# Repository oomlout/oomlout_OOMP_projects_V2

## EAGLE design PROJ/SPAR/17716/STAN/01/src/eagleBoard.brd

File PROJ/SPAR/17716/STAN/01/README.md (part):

Contents
========

* [PRPR17716 > Qwiic Time of Flight TMF8801](#prpr17716--qwiic-time-of-flight-tmf8801)
	* [OOMP Parts](#oomp-parts)
	* [Images](#images)
	* [Tags](#tags)
  
![][im]
# PRPR17716 > Qwiic Time of Flight TMF8801

- ID: PROJ-SPAR-17716-STAN-01
- Hex ID: PRPR17716
- Name: Qwiic Time of Flight TMF8801
- Path: oomlout_OOMP_projects_V2/PROJ/SPAR/17716/STAN/01/
- Description: Qwiic Time of Flight TMF8801
- Long Link: [http://oom.lt/PROJ-SPAR-17716-STAN-01](http://oom.lt/PROJ-SPAR-17716-STAN-01)
- Short Link: [http://oom.lt/PRPR17716](http://oom.lt/PRPR17716)

## OOMP Parts

|Image|OOMP ID|Designators|
| :--- | :--- | :--- |
||[CAPC-0603-X-NF100-V50](https://github.com/oomlout/oomlout_OOMP_parts_V2/tree/main/CAPC/0603/X/NF100/V50/)|[C3,C2,C1](https://github.com/oomlout/oomlout_OOMP_parts_V2/tree/main/CAPC/0603/X/NF100/V50/)|
||[HEAD-I01-X-PI04-01](https://github.com/oomlout/oomlout_OOMP_parts_V2/tree/main/HEAD/I01/X/PI04/01/)|[J4,J3](https://github.com/oomlout/oomlout_OOMP_parts_V2/tree/main/HEAD/I01/X/PI04/01/)|
||[HEAD-JSTSH-X-PI04-RS](https://github.com/oomlout/oomlout_OOMP_parts_V2/tree/main/HEAD/JSTSH/X/PI04/RS/)|[J1,J2](https://github.com/oomlout/oomlout_OOMP_parts_V2/tree/main/HEAD/JSTSH/X/PI04/RS/)|
||[LEDS-0603-R-STAN-01](https://github.com/oomlout/oomlout_OOMP_parts_V2/tree/main/LEDS/0603/R/STAN/01/)|[D1](https://github.com/oomlout/oomlout_OOMP_parts_V2/tree/main/LEDS/0603/R/STAN/01/)|
||[RESE-0603-X-O102-01](https://github.com/oomlout/oomlout_OOMP_parts_V2/tree/main/RESE/0603/X/O102/01/)|[R5](https://github.com/oomlout/oomlout_OOMP_parts_V2/tree/main/RESE/0603/X/O102/01/)|
||[RESE-0603-X-O103-01](https://github.com/oomlout/oomlout_OOMP_parts_V2/tree/main/RESE/0603/X/O103/01/)|[R3,R4](https://github.com/oomlout/oomlout_OOMP_parts_V2/tree/main/RESE/0603/X/O103/01/)|
||[RESE-0603-X-O222-01](https://github.com/oomlout/oomlout_OOMP_parts_V2/tree/main/RESE/0603/X/O222/01/)|[R1,R2](https://github.com/oomlout/oomlout_OOMP_parts_V2/tree/main/RESE/0603/X/O222/01/)|
||UNMATCHED-UNMATCHED-X-UNMATCHED-01|U1|
||||

## Images

|kicadPcb3dFront<br>|kicadPcb3dBack<br>|kicadPcb3d<br>|pcbdraw<br>|
| :---: | :---: | :---: | :---: |
|pcbdrawBack<br>||||

## Tags

|Tag Name|Tag Code|Tag Value|
| :--- | :--- | :--- |
|OOMP Type|oompType|PROJ|
|OOMP Size|oompSize|SPAR|
|OOMP Color|oompColor|17716|
|OOMP Description|oompDesc|STAN|
|OOMP Index|oompIndex|01|
|Full OOMP ID|oompID|PROJ-SPAR-17716-STAN-01|
|Hex ID (short code)|hexID|PRPR17716|
|name|name|Qwiic Time of Flight TMF8801|
|gitRepo|gitRepo|https://github.com/sparkfun/Qwiic_Time-of-Flight-TMF8801|
|gitName|gitName|Qwiic_Time-of-Flight-TMF8801|
|eagleBoard|eagleBoard|/Hardware/Qwiic_TMF8801.brd|
|eagleSchem|eagleSchem|/Hardware/Qwiic_TMF8801.sch|
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
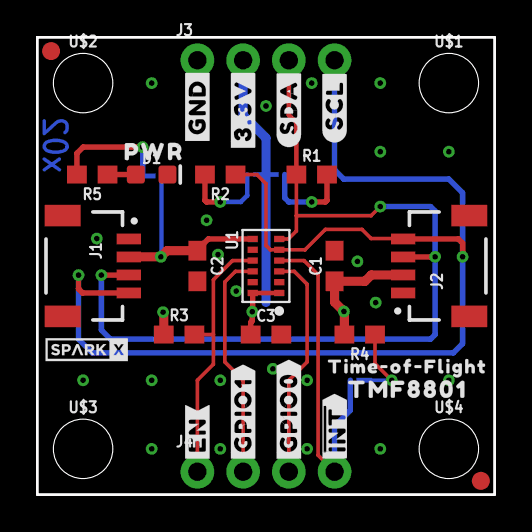
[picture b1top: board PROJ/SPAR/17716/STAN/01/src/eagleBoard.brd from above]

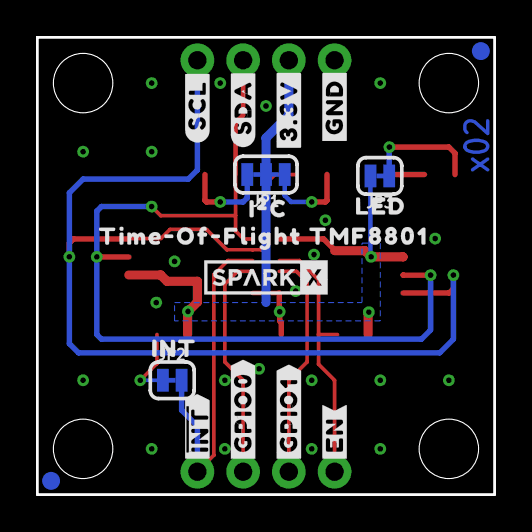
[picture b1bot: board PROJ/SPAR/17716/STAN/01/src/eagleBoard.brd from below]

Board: 2 copper layers, 25.4 x 25.4 mm, 51 parts (18 on the bottom side), 13 nets.

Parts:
C1, C2, C3: 0.1uF; 0603
D1: RED; LED-0603
FD1, FD2, FD3, FD4: FIDUCIAL1X2; FIDUCIAL-1X2
FRAME1: FRAME-LETTERNO_PACKAGE; DUMMY
J1, J2: Qwiic; JST04_1MM_RA
J3, J4: 1X04_NO_SILK
JP1: JUMPER-SMT_3_2-NC_TRACE_SILK; SMT-JUMPER_3_2-NC_TRACE_SILK
JP2, JP3: JUMPER-SMT_2_NC_TRACE_SILK; SMT-JUMPER_2_NC_TRACE_SILK
R1, R2: 2.2k; 0603
R3, R4: 10k; 0603
R5: 1k; 0603
U1: TMF8801; TMF8801-CUSTOM
U$1, U$2, U$3, U$4: STAND-OFF
U$5, U$17: #3#3V#1
U$6, U$19: #SDA#4
U$7, U$18: #GND#0
U$8, U$24: ##INT##7
U$9, U$25: #GPIO0#7
U$10, U$26: #GPIO1#7
U$11, U$23: #EN#6
U$12: #INT0
U$13: TMF88010
U$14: TIME#OF#FLIGHT0
U$16: TIME#OF#FLIGHT_TMF88018
U$20: SPARKX-TINY
U$21, U$22: #SCL#5
U$27: SPARKX-SMALL
U$28: I�C0
U$29: LED1
U$30: PWR2

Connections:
3.3V: C1.1, C2.1, C3.1, J1.2, J2.2, J3.2, JP1.2, JP3.2, R3.2, R4.2, U1.1, U1.7, U1.12
!INT: J4.4, JP2.2, U1.4
EN: J4.1, R3.1, U1.9
GND: C1.2, C2.2, C3.2, D1.C, J1.1, J2.1, J3.1, U1.2, U1.8, U1.11
GPIO0: J4.3, U1.3
GPIO1: J4.2, U1.10
unnamed: D1.A, R5.1
unnamed: JP1.3, R1.2
unnamed: JP1.1, R2.2
unnamed: JP3.1, R5.2
unnamed: JP2.1, R4.1
SCL: J1.4, J2.4, J3.4, R2.1, U1.5
SDA: J1.3, J2.3, J3.3, R1.1, U1.6

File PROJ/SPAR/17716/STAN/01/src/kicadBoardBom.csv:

"Id";"Designator";"Package";"Quantity";"Designation";"Supplier and ref";
1;"FRAME1";"DUMMY";1;"FRAME-LETTERNO_PACKAGE";;;
2;"U$3,U$4,U$2,U$1";"STAND-OFF";4;"";;;
3;"U$5,U$17";"#3#3V#1";2;"";;;
4;"FD1,FD3,FD2,FD4";"FIDUCIAL-1X2";4;"FIDUCIAL1X2";;;
5;"U$14";"TIME#OF#FLIGHT0";1;"";;;
6;"U1";"TMF8801-CUSTOM";1;"TMF8801";;;
7;"D1";"LED-0603";1;"RED";;;
8;"U$8,U$24";"##INT##7";2;"";;;
9;"J4,J3";"1X04_NO_SILK";2;"";;;
10;"U$13";"TMF88010";1;"";;;
11;"U$20";"SPARKX-TINY";1;"";;;
12;"R3,R4";"0603";2;"10k";;;
13;"C3,C2,C1";"0603";3;"0.1uF";;;
14;"U$9,U$25";"#GPIO0#7";2;"";;;
15;"R1,R2";"0603";2;"2.2k";;;
16;"J1,J2";"JST04_1MM_RA";2;"Qwiic";;;
17;"R5";"0603";1;"1k";;;
18;"U$7,U$18";"#GND#0";2;"";;;
19;"U$11,U$23";"#EN#6";2;"";;;
20;"U$6,U$19";"#SDA#4";2;"";;;
21;"U$21,U$22";"#SCL#5";2;"";;;
22;"U$10,U$26";"#GPIO1#7";2;"";;;
23;"U$30";"PWR2";1;"";;;
24;"JP3,JP2";"SMT-JUMPER_2_NC_TRACE_SILK";2;"JUMPER-SMT_2_NC_TRACE_SILK";;;
25;"U$29";"LED1";1;"";;;
26;"U$27";"SPARKX-SMALL";1;"";;;
27;"U$16";"TIME#OF#FLIGHT_TMF88018";1;"";;;
28;"JP1";"SMT-JUMPER_3_2-NC_TRACE_SILK";1;"JUMPER-SMT_3_2-NC_TRACE_SILK";;;
29;"U$28";"I�C0";1;"";;;
30;"U$12";"#INT0";1;"";;;

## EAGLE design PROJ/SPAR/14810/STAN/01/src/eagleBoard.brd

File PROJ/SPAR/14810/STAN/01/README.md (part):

Contents
========

* [PRPR14810 > MP3 Breakout WT2003S](#prpr14810--mp3-breakout-wt2003s)
	* [OOMP Parts](#oomp-parts)
	* [Images](#images)
	* [Tags](#tags)
  
![][im]
# PRPR14810 > MP3 Breakout WT2003S

- ID: PROJ-SPAR-14810-STAN-01
- Hex ID: PRPR14810
- Name: MP3 Breakout WT2003S
- Path: oomlout_OOMP_projects_V2/PROJ/SPAR/14810/STAN/01/
- Description: MP3 Breakout WT2003S
- Long Link: [http://oom.lt/PROJ-SPAR-14810-STAN-01](http://oom.lt/PROJ-SPAR-14810-STAN-01)
- Short Link: [http://oom.lt/PRPR14810](http://oom.lt/PRPR14810)

## OOMP Parts

|Image|OOMP ID|Designators|
| :--- | :--- | :--- |
||[CAPC-0603-X-NF100-V50](https://github.com/oomlout/oomlout_OOMP_parts_V2/tree/main/CAPC/0603/X/NF100/V50/)|[C8,C7](https://github.com/oomlout/oomlout_OOMP_parts_V2/tree/main/CAPC/0603/X/NF100/V50/)|
||CAPC-0603-X-NF220-V25|C6,C3|
||[CAPC-0603-X-UF1-V50](https://github.com/oomlout/oomlout_OOMP_parts_V2/tree/main/CAPC/0603/X/UF1/V50/)|[C5,C4,C9](https://github.com/oomlout/oomlout_OOMP_parts_V2/tree/main/CAPC/0603/X/UF1/V50/)|
||[CAPC-0603-X-UF10-V10](https://github.com/oomlout/oomlout_OOMP_parts_V2/tree/main/CAPC/0603/X/UF10/V10/)|[C1](https://github.com/oomlout/oomlout_OOMP_parts_V2/tree/main/CAPC/0603/X/UF10/V10/)|
||[HEAD-I01-X-PI01-01](https://github.com/oomlout/oomlout_OOMP_parts_V2/tree/main/HEAD/I01/X/PI01/01/)|[J3](https://github.com/oomlout/oomlout_OOMP_parts_V2/tree/main/HEAD/I01/X/PI01/01/)|
||[HEAD-I01-X-PI02-01](https://github.com/oomlout/oomlout_OOMP_parts_V2/tree/main/HEAD/I01/X/PI02/01/)|[J4,JP12](https://github.com/oomlout/oomlout_OOMP_parts_V2/tree/main/HEAD/I01/X/PI02/01/)|
||[HEAD-I01-X-PI03-01](https://github.com/oomlout/oomlout_OOMP_parts_V2/tree/main/HEAD/I01/X/PI03/01/)|[JP10](https://github.com/oomlout/oomlout_OOMP_parts_V2/tree/main/HEAD/I01/X/PI03/01/)|
||[HEAD-I01-X-PI04-01](https://github.com/oomlout/oomlout_OOMP_parts_V2/tree/main/HEAD/I01/X/PI04/01/)|[J2](https://github.com/oomlout/oomlout_OOMP_parts_V2/tree/main/HEAD/I01/X/PI04/01/)|
||HEAD-I01-X-UNMATCHED-01|J1|
||HEAD-UNMATCHED-X-UNMATCHED-01|J8|
||[LEDS-0603-R-STAN-01](https://github.com/oomlout/oomlout_OOMP_parts_V2/tree/main/LEDS/0603/R/STAN/01/)|[D1](https://github.com/oomlout/oomlout_OOMP_parts_V2/tree/main/LEDS/0603/R/STAN/01/)|
||[RESE-0603-X-O102-01](https://github.com/oomlout/oomlout_OOMP_parts_V2/tree/main/RESE/0603/X/O102/01/)|[R2](https://github.com/oomlout/oomlout_OOMP_parts_V2/tree/main/RESE/0603/X/O102/01/)|
||[RESE-0603-X-O103-01](https://github.com/oomlout/oomlout_OOMP_parts_V2/tree/main/RESE/0603/X/O103/01/)|[R5,R10,R9,R1](https://github.com/oomlout/oomlout_OOMP_parts_V2/tree/main/RESE/0603/X/O103/01/)|
||[RESE-0603-X-O222-01](https://github.com/oomlout/oomlout_OOMP_parts_V2/tree/main/RESE/0603/X/O222/01/)|[R4](https://github.com/oomlout/oomlout_OOMP_parts_V2/tree/main/RESE/0603/X/O222/01/)|
||RESE-0603-X-O472-01|R11|
||UNMATCHED-UNMATCHED-X-UNMATCHED-01|U2,U1|
||USBS-UNMATCHED-X-UNMATCHED-01|J6|
||||

## Images

|kicadPcb3dFront<br>|kicadPcb3dBack<br>|kicadPcb3d<br>|pcbdraw<br>|
| :---: | :---: | :---: | :---: |
|pcbdrawBack<br>||||

## Tags

|Tag Name|Tag Code|Tag Value|
| :--- | :--- | :--- |
|OOMP Type|oompType|PROJ|
|OOMP Size|oompSize|SPAR|
|OOMP Color|oompColor|14810|
|OOMP Description|oompDesc|STAN|
|OOMP Index|oompIndex|01|
|Full OOMP ID|oompID|PROJ-SPAR-14810-STAN-01|
|Hex ID (short code)|hexID|PRPR14810|
|name|name|MP3 Breakout WT2003S|
|gitRepo|gitRepo|https://github.com/sparkfun/MP3_Breakout_WT2003S|
|gitName|gitName|MP3_Breakout_WT2003S|
|eagleBoard|eagleBoard|/Hardware/MP3 Breakout.brd|
|eagleSchem|eagleSchem|/Hardware/MP3 Breakout.sch|
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
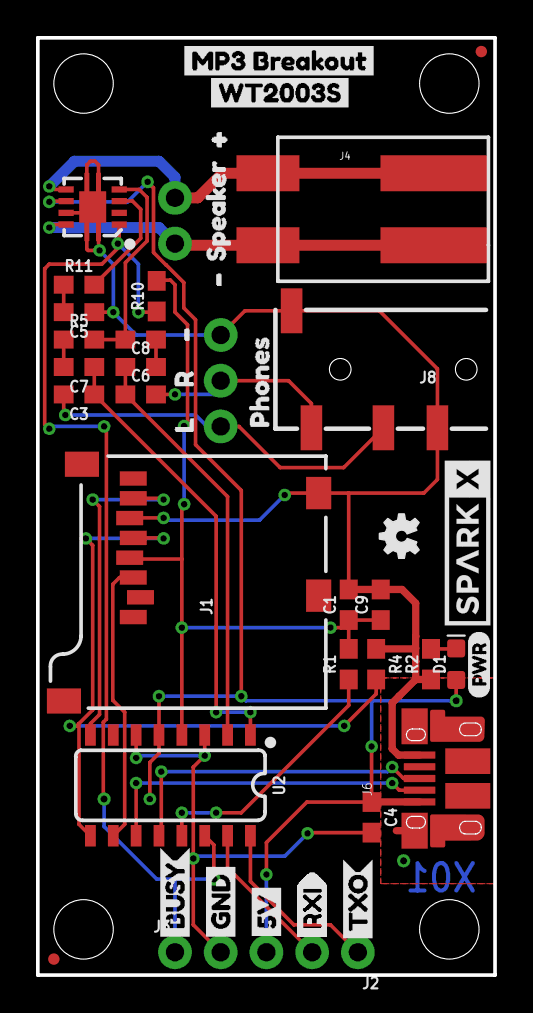
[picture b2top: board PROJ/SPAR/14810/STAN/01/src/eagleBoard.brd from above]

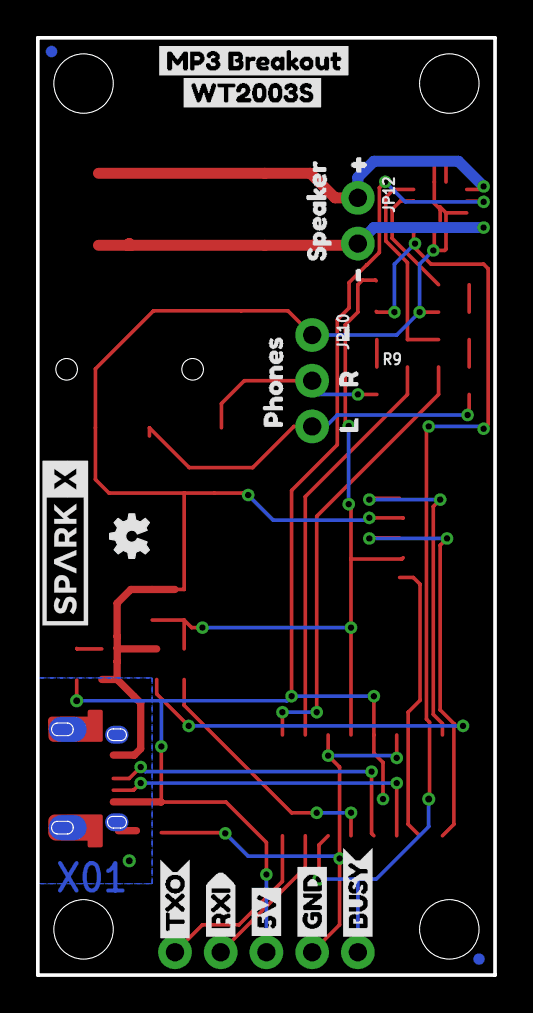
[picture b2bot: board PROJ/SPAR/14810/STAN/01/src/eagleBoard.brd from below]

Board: 2 copper layers, 25.4 x 52.1 mm, 69 parts (20 on the bottom side), 25 nets.

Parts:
C1: 10uF; 0603
C3, C6: 0.22uF; 0603
C4, C5, C9: 1.0uF; 0603
C7, C8: 0.1uF; 0603
D1: RED; LED-0603
FRAME1: FRAME-LETTER; CREATIVE_COMMONS
J1: MICRO-SD; MICRO-SD-SOCKET
J2: Header; 1X04_NO_SILK
J3: 1X01_NO_SILK
J4: Poke-Home; 1X02_POKEHOME
J6: USB-MICROB-PTH-MILL
J8: 3.5mm Audio; AUDIO_JACK_3.5MM_TRRS_SMD_RA
JP1, JP2, JP5, JP6: FIDUCIALUFIDUCIAL; MICRO-FIDUCIAL
JP3, JP4, JP11, JP13: STAND-OFF
JP10: PTH; 1X03_NO_SILK
JP12: PTH; 1X02_NO_SILK
LOGO1: OSHW-LOGOMINI; OSHW-LOGO-MINI
LOGO2: OSHW-LOGOMINI; OSHW-LOGO-MINI@1
R1, R5, R9, R10: 10k; 0603
R2: 1k; 0603
R4: 2.2k; 0603
R11: 100k; 0603
U1: TPA2005D1; QFN-8_PAD
U2: WT2003S; SO16
U$1, U$22: GND1
U$2, U$11: SPARKX-LOGO4; SPARKX-MEDIUM
U$3, U$41: L12
U$4, U$39: R11
U$6, U$9: TXO0
U$7, U$8, U$23: RXI0
U$10, U$15, U$21, U$25: #6
U$12, U$24: MP3_BREAKOUT0
U$13, U$14: BUSY0
U$16, U$40: PHONES0
U$17: PWR-()-03
U$18, U$20: SPEAKER1
U$19, U$28: #5
U$26, U$27: WT2003S0
U$29, U$30: 5V0

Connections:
5V: C4.1, D1.A, J2.3, J6.VBUS, U1.6, U2.5
!SDN: J3.1, R10.1, U1.1, U2.14
AC-L: C3.2, J8.RING1, JP10.3
AC-R: C6.2, J8.TIP, JP10.2
ADKEY: R1.1, U2.13
D+: J6.D+, U2.12
D-: J6.D-, U2.11
GND: C1.2, C4.2, C5.1, C9.2, J1.CD1, J1.GND, J2.4, J6.GND, J8.EARTH, J8.RING2, JP10.1, R2.1, R4.1, U1.7, U1.9, U1.10, U1.11, U1.12, U1.13, U2.3, U2.6
IN+AMP: R11.2, U1.3
IN-AMP: R5.2, R9.2, U1.4
MP3-RXI: J2.2, U2.15
MP3-TXO: J2.1, U2.16
unnamed: D1.C, R2.2
unnamed: C8.2, R9.1
unnamed: C5.2, R11.1
unnamed: C7.2, R5.1
OUT+: J4.P2, J4.P4, JP12.1, U1.5
OUT-: J4.P1, J4.P3, JP12.2, U1.8
SD_CLK: J1.SCLK, R4.2, U2.9
SD_CMD: J1.DI, U2.10
SD_DAT: J1.DO, U2.8
SHLD: J6.SHIELD, J6.SHIELD2, J6.SHIELD3, J6.SHIELD4, J6.SHIELD5, J6.SHIELD6, J6.SHIELD7, J6.SHIELD8, J6.SHIELD9, J6.SHIELD10
VCCIO: C1.1, C9.1, J1.VCC, R1.2, R10.2, U2.4
VOUTL: C3.1, C7.1, U2.1
VOUTR: C6.1, C8.1, U2.2

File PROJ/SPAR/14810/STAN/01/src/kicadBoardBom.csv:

"Id";"Designator";"Package";"Quantity";"Designation";"Supplier and ref";
1;"U$41,U$3";"L12";2;"";;;
2;"C8,C7";"0603";2;"0.1uF";;;
3;"J2";"1X04_NO_SILK";1;"Header";;;
4;"JP4,JP11,JP13,JP3";"STAND-OFF";4;"STAND-OFF";;;
5;"U$20,U$18";"SPEAKER1";2;"";;;
6;"U$10,U$25,U$21,U$15";"#6";4;"";;;
7;"R5,R10,R9,R1";"0603";4;"10k";;;
8;"J4";"1X02_POKEHOME";1;"Poke-Home";;;
9;"J3";"1X01_NO_SILK";1;"";;;
10;"FRAME1";"CREATIVE_COMMONS";1;"FRAME-LETTER";;;
11;"U$12,U$24";"MP3_BREAKOUT0";2;"";;;
12;"J8";"AUDIO_JACK_3.5MM_TRRS_SMD_RA";1;"3.5mm Audio";;;
13;"U$29,U$30";"5V0";2;"";;;
14;"U$23,U$7,U$8";"RXI0";3;"";;;
15;"R4";"0603";1;"2.2k";;;
16;"U$13,U$14";"BUSY0";2;"";;;
17;"D1";"LED-0603";1;"RED";;;
18;"U$26,U$27";"WT2003S0";2;"";;;
19;"C5,C4,C9";"0603";3;"1.0uF";;;
20;"U2";"SO16";1;"WT2003S";;;
21;"R2";"0603";1;"1k";;;
22;"C6,C3";"0603";2;"0.22uF";;;
23;"U1";"QFN-8_PAD";1;"TPA2005D1";;;
24;"U$6,U$9";"TXO0";2;"";;;
25;"U$39,U$4";"R11";2;"";;;
26;"U$2,U$11";"SPARKX-MEDIUM";2;"SPARKX-LOGO4";;;
27;"U$22,U$1";"GND1";2;"";;;
28;"JP1,JP5,JP6,JP2";"MICRO-FIDUCIAL";4;"FIDUCIALUFIDUCIAL";;;
29;"U$17";"PWR-()-03";1;"";;;
30;"J1";"MICRO-SD-SOCKET";1;"MICRO-SD";;;
31;"U$28,U$19";"#5";2;"";;;
32;"J6";"USB-MICROB-PTH-MILL";1;"";;;
33;"R11";"0603";1;"4.7k";;;
34;"C1";"0603";1;"10uF";;;
35;"U$40,U$16";"PHONES0";2;"";;;
36;"LOGO1";"OSHW-LOGO-MINI";1;"OSHW-LOGOMINI";;;
37;"JP10";"1X03_NO_SILK";1;"PTH";;;
38;"LOGO2";"OSHW-LOGO-MINI@1";1;"OSHW-LOGOMINI";;;
39;"JP12";"1X02_NO_SILK";1;"PTH";;;

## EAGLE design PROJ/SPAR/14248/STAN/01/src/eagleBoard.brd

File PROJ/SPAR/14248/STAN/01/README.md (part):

Contents
========

* [PRPR14248 > Qwiic Accelerometer MMA8452Q](#prpr14248--qwiic-accelerometer-mma8452q)
	* [OOMP Parts](#oomp-parts)
	* [Images](#images)
	* [Tags](#tags)
  
![][im]
# PRPR14248 > Qwiic Accelerometer MMA8452Q

- ID: PROJ-SPAR-14248-STAN-01
- Hex ID: PRPR14248
- Name: Qwiic Accelerometer MMA8452Q
- Path: oomlout_OOMP_projects_V2/PROJ/SPAR/14248/STAN/01/
- Description: Qwiic Accelerometer MMA8452Q
- Long Link: [http://oom.lt/PROJ-SPAR-14248-STAN-01](http://oom.lt/PROJ-SPAR-14248-STAN-01)
- Short Link: [http://oom.lt/PRPR14248](http://oom.lt/PRPR14248)

## OOMP Parts

|Image|OOMP ID|Designators|
| :--- | :--- | :--- |
||[CAPC-0603-X-NF100-V50](https://github.com/oomlout/oomlout_OOMP_parts_V2/tree/main/CAPC/0603/X/NF100/V50/)|[C1,C4](https://github.com/oomlout/oomlout_OOMP_parts_V2/tree/main/CAPC/0603/X/NF100/V50/)|
||[CAPC-0603-X-UF47D-V16](https://github.com/oomlout/oomlout_OOMP_parts_V2/tree/main/CAPC/0603/X/UF47D/V16/)|[C5](https://github.com/oomlout/oomlout_OOMP_parts_V2/tree/main/CAPC/0603/X/UF47D/V16/)|
||[HEAD-I01-X-PI02-01](https://github.com/oomlout/oomlout_OOMP_parts_V2/tree/main/HEAD/I01/X/PI02/01/)|[J1](https://github.com/oomlout/oomlout_OOMP_parts_V2/tree/main/HEAD/I01/X/PI02/01/)|
||[HEAD-I01-X-PI04-01](https://github.com/oomlout/oomlout_OOMP_parts_V2/tree/main/HEAD/I01/X/PI04/01/)|[J3](https://github.com/oomlout/oomlout_OOMP_parts_V2/tree/main/HEAD/I01/X/PI04/01/)|
||[HEAD-JSTSH-X-PI04-RS](https://github.com/oomlout/oomlout_OOMP_parts_V2/tree/main/HEAD/JSTSH/X/PI04/RS/)|[J2,J4](https://github.com/oomlout/oomlout_OOMP_parts_V2/tree/main/HEAD/JSTSH/X/PI04/RS/)|
||[RESE-0603-X-O103-01](https://github.com/oomlout/oomlout_OOMP_parts_V2/tree/main/RESE/0603/X/O103/01/)|[R2](https://github.com/oomlout/oomlout_OOMP_parts_V2/tree/main/RESE/0603/X/O103/01/)|
||RESE-0603-X-O472-01|R5,R4|
||UNMATCHED-UNMATCHED-X-UNMATCHED-01|U2|
||||

## Images

|kicadPcb3dFront<br>|kicadPcb3dBack<br>|kicadPcb3d<br>|pcbdraw<br>|
| :---: | :---: | :---: | :---: |
|pcbdrawBack<br>||||

## Tags

|Tag Name|Tag Code|Tag Value|
| :--- | :--- | :--- |
|OOMP Type|oompType|PROJ|
|OOMP Size|oompSize|SPAR|
|OOMP Color|oompColor|14248|
|OOMP Description|oompDesc|STAN|
|OOMP Index|oompIndex|01|
|Full OOMP ID|oompID|PROJ-SPAR-14248-STAN-01|
|Hex ID (short code)|hexID|PRPR14248|
|name|name|Qwiic Accelerometer MMA8452Q|
|gitRepo|gitRepo|https://github.com/sparkfun/Qwiic_Accelerometer-MMA8452Q|
|gitName|gitName|Qwiic_Accelerometer-MMA8452Q|
|eagleBoard|eagleBoard|/Hardware/Qwiic_Accelerometer-MMA8452Q.brd|
|eagleSchem|eagleSchem|/Hardware/Qwiic_Accelerometer-MMA8452Q.sch|
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
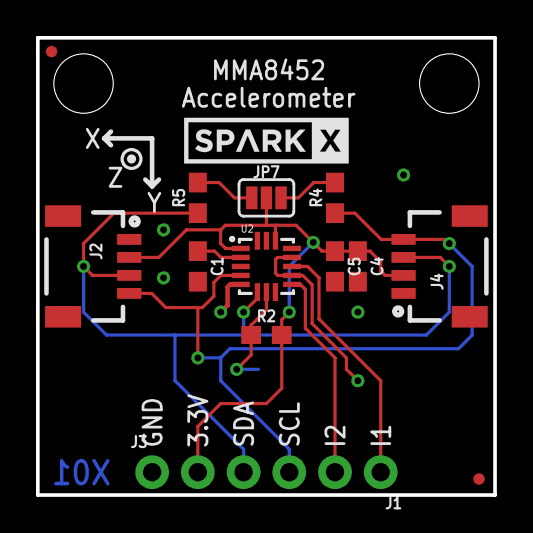
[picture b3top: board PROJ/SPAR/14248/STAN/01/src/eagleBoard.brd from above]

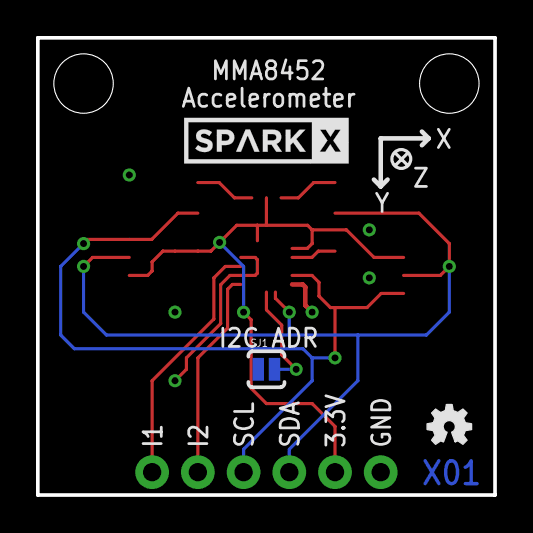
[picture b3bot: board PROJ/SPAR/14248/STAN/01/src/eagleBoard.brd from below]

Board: 2 copper layers, 25.4 x 25.4 mm, 21 parts (3 on the bottom side), 10 nets.

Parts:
C1, C4: 0.1uF; 0603
C5: 4.7uF; 0603
FRAME1: FRAME-LETTER; CREATIVE_COMMONS
J1: 1X02_NO_SILK
J2, J4: SMD; 1X04_1MM_RA
J3: PTH; 1X04_NO_SILK
JP2, JP6: FIDUCIALUFIDUCIAL; MICRO-FIDUCIAL
JP3, JP4: STAND-OFF
JP7: SMT-JUMPER_3_2-NC_PASTE_SILK
LOGO1: OSHW-LOGOMINI; OSHW-LOGO-MINI
R2: 10k; 0603
R4, R5: 4.7k; 0603
SJ1: SJ_2S-NO
U2: MMA8452Q; QFN-16_0.5MM
U$1, U$2: SPARKX-LOGO4; SPARKX-MEDIUM

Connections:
3.3V: C4.1, C5.1, J2.2, J3.2, J4.2, JP7.2, R2.2, U2.1, U2.14
BYP: C1.1, U2.2
GND: C1.2, C4.2, C5.2, J2.1, J3.1, J4.1, SJ1.1, U2.5, U2.10, U2.12
INT1: J1.1, U2.11
INT2: J1.2, U2.9
unnamed: JP7.1, R5.2
unnamed: JP7.3, R4.2
SA0: R2.1, SJ1.2, U2.7
SCL: J2.4, J3.4, J4.4, R4.1, U2.4
SDA: J2.3, J3.3, J4.3, R5.1, U2.6

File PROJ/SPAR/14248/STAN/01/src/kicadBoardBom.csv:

"Id";"Designator";"Package";"Quantity";"Designation";"Supplier and ref";
1;"JP3,JP4";"STAND-OFF";2;"STAND-OFF";;;
2;"R5,R4";"0603";2;"4.7k";;;
3;"JP7";"SMT-JUMPER_3_2-NC_PASTE_SILK";1;"";;;
4;"JP2,JP6";"MICRO-FIDUCIAL";2;"FIDUCIALUFIDUCIAL";;;
5;"C1,C4";"0603";2;"0.1uF";;;
6;"U2";"QFN-16_0.5MM";1;"MMA8452Q";;;
7;"J3";"1X04_NO_SILK";1;"PTH";;;
8;"J1";"1X02_NO_SILK";1;"";;;
9;"R2";"0603";1;"10k";;;
10;"U$2,U$1";"SPARKX-MEDIUM";2;"SPARKX-LOGO4";;;
11;"FRAME1";"CREATIVE_COMMONS";1;"FRAME-LETTER";;;
12;"C5";"0603";1;"4.7uF";;;
13;"J2,J4";"1X04_1MM_RA";2;"SMD";;;
14;"LOGO1";"OSHW-LOGO-MINI";1;"OSHW-LOGOMINI";;;
15;"SJ1";"SJ_2S-NO";1;"";;;

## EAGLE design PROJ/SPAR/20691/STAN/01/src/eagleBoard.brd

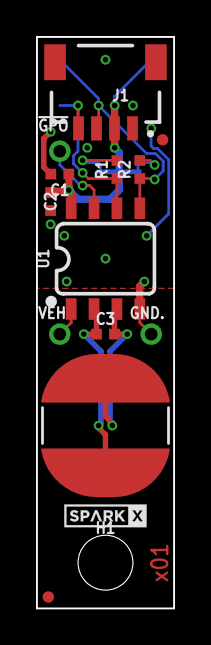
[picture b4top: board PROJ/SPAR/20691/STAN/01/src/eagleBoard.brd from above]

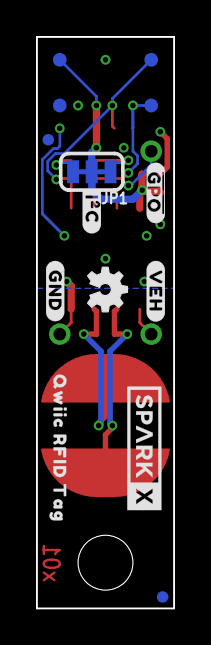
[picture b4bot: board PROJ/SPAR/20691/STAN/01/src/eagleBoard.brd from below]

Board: 2 copper layers, 7.6 x 31.8 mm, 31 parts (14 on the bottom side), 10 nets.

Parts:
3V3: TEST-POINT3; PAD.03X.03
!GPO!: 1X01_1MM_NO_SILK
ANT: 4.7μH; W3102
C1: 0.1uF; 0402-TIGHT
C2: 2.2uF; 0402-TIGHT
C3: 0.5pF; 0402-TIGHT
FD1, FD2, FD3, FD4: FIDUCIALUFIDUCIAL; FIDUCIAL-MICRO
FRAME2: FRAME-LETTER; CREATIVE_COMMONS
GND: TEST-POINT3; PAD.03X.03
GND.: 1X01_1MM_NO_SILK
H1: STAND-OFFTIGHT; STAND-OFF-TIGHT
J1: QWIIC_RIGHT_ANGLE; JST04_1MM_RA
JP1: JUMPER-SMT_3_2-NC_TRACE_SILK; SMT-JUMPER_3_2-NC_TRACE_SILK
LOGO1: SPECIAL_INSTRUCTIONS-ORDERING; ORDERING_INSTRUCTIONS
LOGO2: OSHW-LOGOMINI; OSHW-LOGO-MINI
R1, R2: 2.2k; 0402-TIGHT
SCL: TEST-POINT3; PAD.03X.03
SDA: TEST-POINT3; PAD.03X.03
U1: ST25DV64KC; SO08
U$1: SPARKX-LOGO2; SPARKX-TINY
U$2: ##GPO##0
U$3: QWIIC_RFID_TAG0
U$4: #VEH#0
U$5: #I�C#0
U$6: #GND#0
U$20: SPARKX-LOGO3; SPARKX-SMALL
VEH: 1X01_1MM_NO_SILK

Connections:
3.3V: 3V3.1, C1.1, C2.1, J1.2, JP1.2, U1.8
!GPO!: !GPO!.1, U1.7
GND: C1.2, C2.2, GND.1, GND..1, J1.1, U1.4
unnamed: ANT.2, C3.2, U1.3
unnamed: ANT.1, C3.1, U1.2
unnamed: JP1.3, R2.2
unnamed: JP1.1, R1.2
SCL: J1.4, R1.1, SCL.1, U1.6
SDA: J1.3, R2.1, SDA.1, U1.5
VEH: U1.1, VEH.1

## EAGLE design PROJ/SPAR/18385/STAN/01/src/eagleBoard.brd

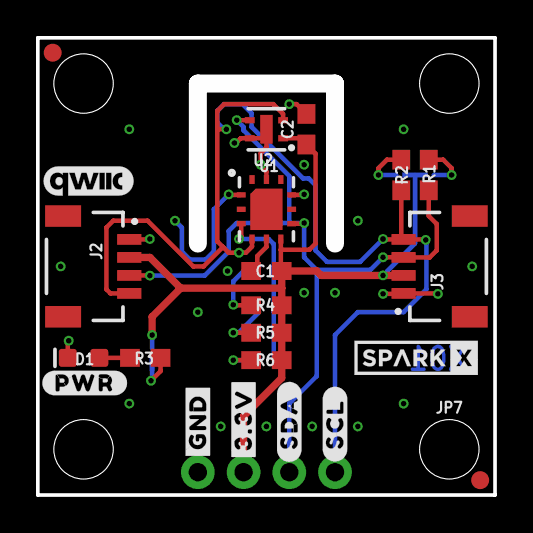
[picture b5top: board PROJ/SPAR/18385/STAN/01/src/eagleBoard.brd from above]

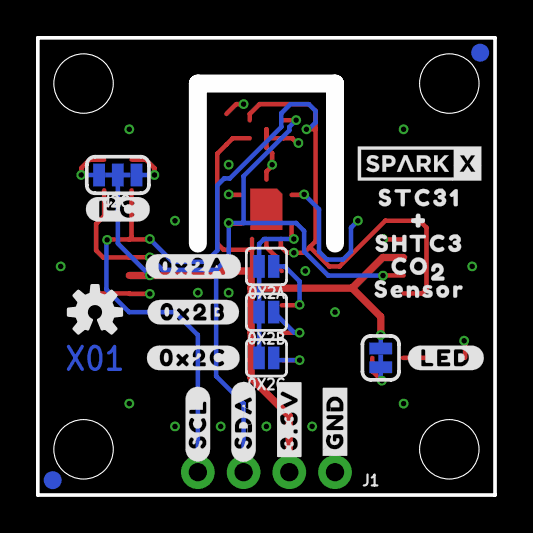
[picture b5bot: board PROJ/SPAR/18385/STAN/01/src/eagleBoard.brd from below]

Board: 2 copper layers, 25.4 x 25.4 mm, 53 parts (25 on the bottom side), 12 nets.

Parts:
0X2A, 0X2B, 0X2C: JUMPER-SMT_2_NO_SILK; SMT-JUMPER_2_NO_SILK
C1, C2: 0.1uF; 0603
D1: RED; LED-0603
FRAME1: FRAME-LETTER; CREATIVE_COMMONS
I2C: JUMPER-SMT_3_2-NC_TRACE_SILK; SMT-JUMPER_3_2-NC_TRACE_SILK
J1: 1X04_NO_SILK
J2, J3: QWIIC_RIGHT_ANGLE; JST04_1MM_RA
JP1, JP2, JP5, JP6: FIDUCIAL1X2; FIDUCIAL-1X2
JP3, JP4, JP7, JP8: STAND-OFF
LED: JUMPER-SMT_2_NC_TRACE_SILK; SMT-JUMPER_2_NC_TRACE_SILK
LOGO1: SPECIAL_INSTRUCTIONS-ORDERING; ORDERING_INSTRUCTIONS
LOGO2: QWIIC_LOGO_5MM; QWIIC_5MM
LOGO5: OSHW-LOGOS; OSHW-LOGO-S
R1, R2: 4.7k; 0603
R3, R6: 1k; 0603
R4: 10k; 0603
R5: 3.3k; 0603
U1: STC31
U2: SHTC3
U$1, U$33: #GND#0
U$2, U$34: #3#3V#0
U$3, U$35: #SDA#0
U$4, U$36: #SCL#0
U$5: #LED#0
U$6: #0X2A#0
U$7: #0X2B#0
U$8: #0X2C#0
U$9: #I�C#0
U$10, U$18: SPARKX-LOGO3; SPARKX-SMALL
U$11: STC310
U$12: #0
U$13: SHTC30
U$14: CO0
U$15: 20
U$16: SENSOR0
U$32: #PWR#0

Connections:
3.3V: C1.1, C2.1, I2C.2, J1.2, J2.2, J3.2, LED.2, R4.1, R5.1, R6.1, U1.6, U2.1
ADDR: 0X2A.2, 0X2B.2, 0X2C.2, U1.3
GND: C1.2, C2.2, D1.C, J1.1, J2.1, J3.1, U1.1, U1.5, U1.9, U1.11, U1.DIEPAD, U2.4, U2.5
unnamed: LED.1, R3.2
unnamed: I2C.3, R1.2
unnamed: D1.A, R3.1
unnamed: I2C.1, R2.2
unnamed: 0X2A.1, R4.2
unnamed: 0X2B.1, R5.2
unnamed: 0X2C.1, R6.2
SCL: J1.4, J2.4, J3.4, R2.1, U1.4, U2.2
SDA: J1.3, J2.3, J3.3, R1.1, U1.7, U2.3

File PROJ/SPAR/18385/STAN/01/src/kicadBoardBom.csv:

"Id";"Designator";"Package";"Quantity";"Designation";"Supplier and ref";
1;"C2,C1";"0603";2;"0.1uF";;;
2;"J3,J2";"JST04_1MM_RA";2;"QWIIC_RIGHT_ANGLE";;;
3;"LOGO2";"QWIIC_5MM";1;"QWIIC_LOGO_5MM";;;
4;"JP4,JP7,JP3,JP8";"STAND-OFF";4;"STAND-OFF";;;
5;"FRAME1";"CREATIVE_COMMONS";1;"FRAME-LETTER";;;
6;"U$35,U$3";"#SDA#0";2;"";;;
7;"R1,R2";"0603";2;"4.7k";;;
8;"D1";"LED-0603";1;"RED";;;
9;"LOGO1";"ORDERING_INSTRUCTIONS";1;"SPECIAL_INSTRUCTIONS-ORDERING";;;
10;"U$36,U$4";"#SCL#0";2;"";;;
11;"U$10,U$18";"SPARKX-SMALL";2;"SPARKX-LOGO3";;;
12;"U2";"SHTC3";1;"SHTC3";;;
13;"R5";"0603";1;"3.3k";;;
14;"R4";"0603";1;"10k";;;
15;"R3,R6";"0603";2;"1k";;;
16;"JP2,JP6,JP1,JP5";"FIDUCIAL-1X2";4;"FIDUCIAL1X2";;;
17;"U$33,U$1";"#GND#0";2;"";;;
18;"U$32";"#PWR#0";1;"";;;
19;"U$34,U$2";"#3#3V#0";2;"";;;
20;"U1";"STC31";1;"STC31";;;
21;"UNK0X2B0,UNK0X2C0,UNK0X2A0";"SMT-JUMPER_2_NO_SILK";3;"JUMPER-SMT_2_NO_SILK";;;
22;"U$7";"#0X2B#0";1;"";;;
23;"U$11";"STC310";1;"";;;
24;"U$13";"SHTC30";1;"";;;
25;"U$9";"#I�C#0";1;"";;;
26;"U$6";"#0X2A#0";1;"";;;
27;"U$5";"#LED#0";1;"";;;
28;"LOGO5";"OSHW-LOGO-S";1;"OSHW-LOGOS";;;
29;"U$12";"#0";1;"";;;
30;"J1";"1X04_NO_SILK";1;"";;;
31;"U$8";"#0X2C#0";1;"";;;
32;"U$14";"CO0";1;"";;;
33;"I2C0";"SMT-JUMPER_3_2-NC_TRACE_SILK";1;"JUMPER-SMT_3_2-NC_TRACE_SILK";;;
34;"U$15";"20";1;"";;;
35;"U$16";"SENSOR0";1;"";;;
36;"LED0";"SMT-JUMPER_2_NC_TRACE_SILK";1;"JUMPER-SMT_2_NC_TRACE_SILK";;;

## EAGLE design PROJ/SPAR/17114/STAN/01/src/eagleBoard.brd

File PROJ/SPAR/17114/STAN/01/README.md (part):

Contents
========

* [PRPR17114 > Qwiic Cellular Notecarrier](#prpr17114--qwiic-cellular-notecarrier)
	* [OOMP Parts](#oomp-parts)
	* [Images](#images)
	* [Tags](#tags)
  
![][im]
# PRPR17114 > Qwiic Cellular Notecarrier

- ID: PROJ-SPAR-17114-STAN-01
- Hex ID: PRPR17114
- Name: Qwiic Cellular Notecarrier
- Path: oomlout_OOMP_projects_V2/PROJ/SPAR/17114/STAN/01/
- Description: Qwiic Cellular Notecarrier
- Long Link: [http://oom.lt/PROJ-SPAR-17114-STAN-01](http://oom.lt/PROJ-SPAR-17114-STAN-01)
- Short Link: [http://oom.lt/PRPR17114](http://oom.lt/PRPR17114)

## OOMP Parts

|Image|OOMP ID|Designators|
| :--- | :--- | :--- |
||[CAPC-0603-X-NF100-V50](https://github.com/oomlout/oomlout_OOMP_parts_V2/tree/main/CAPC/0603/X/NF100/V50/)|[C6](https://github.com/oomlout/oomlout_OOMP_parts_V2/tree/main/CAPC/0603/X/NF100/V50/)|
||CAPC-0603-X-NF220-V25|C7|
||[CAPC-0603-X-UF1-V50](https://github.com/oomlout/oomlout_OOMP_parts_V2/tree/main/CAPC/0603/X/UF1/V50/)|[C5,C17,C18](https://github.com/oomlout/oomlout_OOMP_parts_V2/tree/main/CAPC/0603/X/UF1/V50/)|
||[CAPC-0603-X-UF47D-V16](https://github.com/oomlout/oomlout_OOMP_parts_V2/tree/main/CAPC/0603/X/UF47D/V16/)|[C4,C3](https://github.com/oomlout/oomlout_OOMP_parts_V2/tree/main/CAPC/0603/X/UF47D/V16/)|
||CAPX-1210-X-UF22-01|C1|
||DIOD-S323-X-UNMATCHED-01|D4,D1,D6|
||[HEAD-I01-X-PI01-01](https://github.com/oomlout/oomlout_OOMP_parts_V2/tree/main/HEAD/I01/X/PI01/01/)|[J13,J9](https://github.com/oomlout/oomlout_OOMP_parts_V2/tree/main/HEAD/I01/X/PI01/01/)|
||[HEAD-I01-X-PI02-01](https://github.com/oomlout/oomlout_OOMP_parts_V2/tree/main/HEAD/I01/X/PI02/01/)|[J4,J2,J7](https://github.com/oomlout/oomlout_OOMP_parts_V2/tree/main/HEAD/I01/X/PI02/01/)|
||[HEAD-I01-X-PI04-01](https://github.com/oomlout/oomlout_OOMP_parts_V2/tree/main/HEAD/I01/X/PI04/01/)|[J14](https://github.com/oomlout/oomlout_OOMP_parts_V2/tree/main/HEAD/I01/X/PI04/01/)|
||[HEAD-I01-X-PI06-01](https://github.com/oomlout/oomlout_OOMP_parts_V2/tree/main/HEAD/I01/X/PI06/01/)|[J6](https://github.com/oomlout/oomlout_OOMP_parts_V2/tree/main/HEAD/I01/X/PI06/01/)|
||[HEAD-I01-X-PI07-01](https://github.com/oomlout/oomlout_OOMP_parts_V2/tree/main/HEAD/I01/X/PI07/01/)|[J16](https://github.com/oomlout/oomlout_OOMP_parts_V2/tree/main/HEAD/I01/X/PI07/01/)|
||[HEAD-I01-X-PI10-01](https://github.com/oomlout/oomlout_OOMP_parts_V2/tree/main/HEAD/I01/X/PI10/01/)|[J5](https://github.com/oomlout/oomlout_OOMP_parts_V2/tree/main/HEAD/I01/X/PI10/01/)|
||HEAD-I01-X-UNMATCHED-01|J10,J12,J15|
||[HEAD-JSTSH-X-PI04-RS](https://github.com/oomlout/oomlout_OOMP_parts_V2/tree/main/HEAD/JSTSH/X/PI04/RS/)|[J8,J3](https://github.com/oomlout/oomlout_OOMP_parts_V2/tree/main/HEAD/JSTSH/X/PI04/RS/)|
||[LEDS-0603-R-STAN-01](https://github.com/oomlout/oomlout_OOMP_parts_V2/tree/main/LEDS/0603/R/STAN/01/)|[D5](https://github.com/oomlout/oomlout_OOMP_parts_V2/tree/main/LEDS/0603/R/STAN/01/)|
||[LEDS-0603-Y-STAN-01](https://github.com/oomlout/oomlout_OOMP_parts_V2/tree/main/LEDS/0603/Y/STAN/01/)|[D2](https://github.com/oomlout/oomlout_OOMP_parts_V2/tree/main/LEDS/0603/Y/STAN/01/)|
||[RESE-0603-X-O102-01](https://github.com/oomlout/oomlout_OOMP_parts_V2/tree/main/RESE/0603/X/O102/01/)|[R7,R11](https://github.com/oomlout/oomlout_OOMP_parts_V2/tree/main/RESE/0603/X/O102/01/)|
||[RESE-0603-X-O222-01](https://github.com/oomlout/oomlout_OOMP_parts_V2/tree/main/RESE/0603/X/O222/01/)|[R6,R4,R1](https://github.com/oomlout/oomlout_OOMP_parts_V2/tree/main/RESE/0603/X/O222/01/)|
||RESE-0603-X-O472-01|R3,R2|
||UNMATCHED-SO235-X-UNMATCHED-01|U1,U2|
||UNMATCHED-UNMATCHED-X-UNMATCHED-01|S1,E3,E4,U4|
||USBS-UNMATCHED-X-UNMATCHED-01|J1|
||||

## Images

|kicadPcb3dFront<br>|kicadPcb3dBack<br>|kicadPcb3d<br>|pcbdraw<br>|
| :---: | :---: | :---: | :---: |
|pcbdrawBack<br>||||

## Tags

|Tag Name|Tag Code|Tag Value|
| :--- | :--- | :--- |
|OOMP Type|oompType|PROJ|
|OOMP Size|oompSize|SPAR|
|OOMP Color|oompColor|17114|
|OOMP Description|oompDesc|STAN|
|OOMP Index|oompIndex|01|
|Full OOMP ID|oompID|PROJ-SPAR-17114-STAN-01|
|Hex ID (short code)|hexID|PRPR17114|
|name|name|Qwiic Cellular Notecarrier|
|gitRepo|gitRepo|https://github.com/sparkfun/Qwiic_Cellular-Notecarrier|
|gitName|gitName|Qwiic_Cellular-Notecarrier|
|eagleBoard|eagleBoard|/Hardware/Qwiic-Cellular-Notepad.brd|
|eagleSchem|eagleSchem|/Hardware/Qwiic-Cellular-Notepad.sch|
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
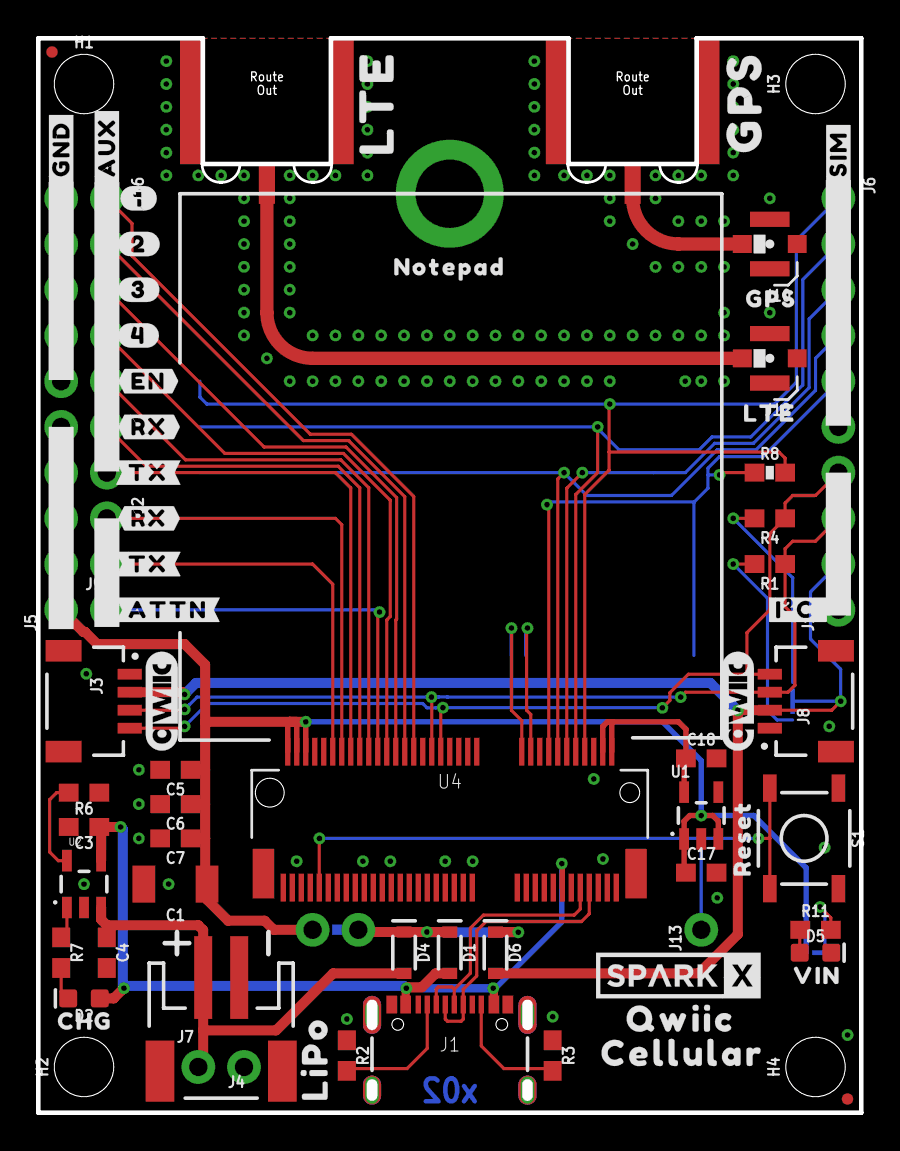
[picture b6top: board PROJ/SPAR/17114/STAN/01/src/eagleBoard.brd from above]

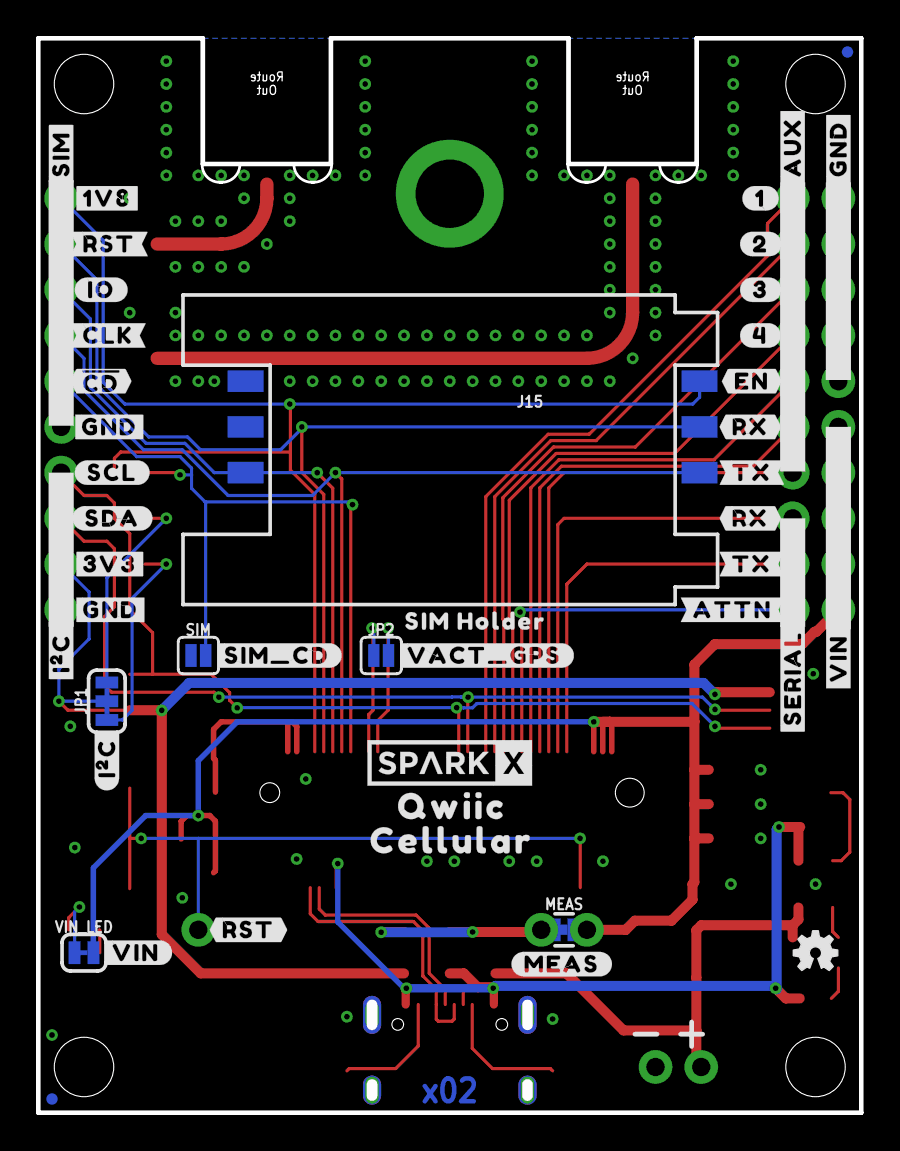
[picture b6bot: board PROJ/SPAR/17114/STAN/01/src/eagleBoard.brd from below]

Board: 2 copper layers, 45.7 x 59.7 mm, 122 parts (45 on the bottom side), 40 nets.

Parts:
C1: 22uF; 1210
C3, C4: 4.7uF; 0603
C5, C17, C18: 1.0uF; 0603
C6: 0.1uF; 0603
C7: 0.22uF; 0603
D1, D4, D6: 3A/10V/280mV; SOD-323
D2: Yellow; LED-0603
D5: RED; LED-0603
E3, E4: SMA; SMA-EDGE-SMD
FD1, FD2, FD3, FD4: FIDUCIALUFIDUCIAL; FIDUCIAL-MICRO
FRAME1: FRAME-LEDGER; CREATIVE_COMMONS
H1, H2, H3, H4: STAND-OFF
H5: STAND-OFF; STAND-OFF-REFLOW-M2.5
J1: USB-C-16P-2LAYER-PADS
J2, J7: 1X02_NO_SILK
J3, J8: QWIIC_RIGHT_ANGLE; JST04_1MM_RA
J4: JST-2-SMD
J5: 1X10_NO_SILK
J6: External SIM; 1X06_NO_SILK
J9, J13: 1X01_NO_SILK
J10, J12: U.FL
J14: I2C; 1X04_NO_SILK
J15: SIM Socket; SIMHOLDER
J16: 1X07_NO_SILK
JP1: SMT-JUMPER_3_2-NC_TRACE_SILK
JP2: GPS_ANT_PWR; SMT-JUMPER_2_NO_SILK
LOGO2, LOGO5: QWIIC_LOGO_CONNECTOR; QWIIC_5.5MM
LOGO3: OSHW-LOGOMINI; OSHW-LOGO-MINI
MEAS: COMBO-JUMPER_2_NC_TRACE
R1, R4, R6: 2.2k; 0603
R2, R3: 5.1k; 0603
R7, R11: 1k; 0603
R8: DNP; 0603-RES
S1: Reset; TACTILE_SWITCH_SMD_5.2MM
SIM: SMT-JUMPER_2_NO_SILK
U1: STLQ015-3.3V; SOT23-5
U2: MCP73831; SOT23-5
U4: BLUES NOTECARD; M.2-CONNECTOR-E
U$1, U$41: #1#1
U$2: #3V3#2
U$3, U$18, U$22: #GND#0
U$4, U$42: #2#2
U$5, U$43: #3#3
U$6, U$44: #4#4
U$7: GPS_0
U$8: #SERIAL#1
U$9, U$53: #I�C_#0
U$10: #I�C#0
U$11, U$40: #AUX#0
U$12: LTE_1
U$13: #GND#3
U$14, U$46: #RX#6
U$15: LIPO0
U$16, U$47: #TX#5
U$17: #SCL#1
U$19, U$45: #EN#0
U$20: NOTEPAD0
U$21: #SDA#0
U$23: #VIN#0
U$24: #VACT_GPS#0
U$25: #SIM_CD#0
U$26, U$31: QWIIC0
U$27: SIM_HOLDER0
U$28: #MEAS#3
U$29, U$32: CELLULAR1
U$30: #RST#0
U$33: #VIN#1
U$34: ##CD##1
U$35: #1V8#4
U$36: #CLK#3
U$37: #IO#2
U$38: #RST#5
U$39, U$51: #SIM#0
U$48, U$52: #RX#0
U$49, U$54: #TX#1
U$50, U$55: #ATTN#2
U$56, U$57: SPARKX-LOGO4; SPARKX-MEDIUM
U$58: GPS0
U$59: LTE1
U$92: RESET1
U$94: VIN1
U$96: CHG1
VIN_LED: SMT-JUMPER_2_NC_TRACE_SILK

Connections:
3.3V: D6.A, J3.2, J8.2, J14.2, JP1.2
!RESET!: J13.1, S1.3, S1.4, U4.67
ATTN: J9.1, U4.54
AUX1: J16.1, U4.46
AUX2: J16.2, U4.48
AUX3: J16.3, U4.50
AUX4: J16.4, U4.52
AUX_EN: J16.5, U4.56
AUX_RX: J16.6, U4.58
AUX_TX: J16.7, U4.60
CHG_LED: R7.1, U2.1
GND: C1.2, C3.2, C4.2, C5.2, C6.2, C7.2, C17.2, C18.2, D5.C, E3.GND@0, E3.GND@1, E4.GND@0, E4.GND@1, H5.1, J1.GND, J1.GND2, J3.1, J4.1, J5.6, J5.7, J5.8, J5.9, J5.10, J6.6, J7.2, J8.1, J10.1, J10.2, J12.1, J12.2, J14.1, J15.C5, R2.1, R3.1, R6.1, S1.1, S1.2, SIM.1, U1.2, U2.2, U4.3, U4.5, U4.6, U4.11, U4.18, U4.33, U4.39, U4.45, U4.51, U4.57, U4.71, U4.73
unnamed: JP1.3, R4.2
unnamed: JP1.1, R1.2
unnamed: D2.C, R7.2
unnamed: D5.A, R11.1
unnamed: R11.2, VIN_LED.1
unnamed: R6.2, U2.5
unnamed: J1.A5, R2.2
unnamed: J1.B5, R3.2
RF_GPS: E4.SIG, J10.FEED
RF_LTE: E3.SIG, J12.FEED
RX: J2.1, U4.62
SCL: J3.4, J8.4, J14.4, R4.1, U4.40
SDA: J3.3, J8.3, J14.3, R1.1, U4.42
SIM_!CD!: J6.5, R8.1, SIM.2, U4.16
SIM_CLK: J6.4, J15.C3, U4.14
SIM_IO: J6.3, J15.C7, U4.12
SIM_RST: J6.2, J15.C2, U4.10
SIM_VCC: J6.1, J15.C1, R8.2, U4.8
TX: J2.2, U4.64
USB_D+: J1.A6, J1.B6, U4.7
USB_D-: J1.A7, J1.B7, U4.9
VACT_GPS_IN: JP2.2, U4.22
VACT_GPS_OUT: JP2.1, U4.20
VIN: C1.1, C5.1, C6.1, C7.1, C17.1, J5.1, J5.2, J5.3, J5.4, J5.5, MEAS.2, MEAS.4, U1.1, U1.3, U4.70, U4.72, U4.74, VIN_LED.2
VIN1: D1.C, D4.C, D6.C, MEAS.1, MEAS.3
VIO: C18.1, U1.5, U4.2, U4.4
V_BATT: C4.1, D4.A, J4.2, J7.1, U2.3
V_USB: C3.1, D1.A, D2.A, J1.VBUS1, J1.VBUS2, U2.4, U4.13

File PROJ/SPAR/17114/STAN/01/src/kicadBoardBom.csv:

"Id";"Designator";"Package";"Quantity";"Designation";"Supplier and ref";
1;"U$31,U$26";"QWIIC0";2;"";;;
2;"FD2,FD1,FD3,FD4";"FIDUCIAL-MICRO";4;"FIDUCIALUFIDUCIAL";;;
3;"U$53,U$9";"#I�C_#0";2;"";;;
4;"H2,H4,H3,H1";"STAND-OFF";4;"STAND-OFF";;;
5;"U$96";"CHG1";1;"";;;
6;"J5";"1X10_NO_SILK";1;"";;;
7;"R3,R2";"0603";2;"5.1k";;;
8;"U$20";"NOTEPAD0";1;"";;;
9;"U$92";"RESET1";1;"";;;
10;"U$50,U$55";"#ATTN#2";2;"";;;
11;"R7,R11";"0603";2;"1k";;;
12;"J14";"1X04_NO_SILK";1;"I2C";;;
13;"U$22,U$18,U$3";"#GND#0";3;"";;;
14;"U$51,U$39";"#SIM#0";2;"";;;
15;"J1";"USB-C-16P-2LAYER-PADS";1;"";;;
16;"U$7";"GPS_0";1;"";;;
17;"U1";"SOT23-5";1;"STLQ015-3.3V";;;
18;"S1";"TACTILE_SWITCH_SMD_5.2MM";1;"Reset";;;
19;"R8";"0603-RES";1;"DNP";;;
20;"J13,J9";"1X01_NO_SILK";2;"";;;
21;"D4,D1,D6";"SOD-323";3;"3A/10V/280mV";;;
22;"J16";"1X07_NO_SILK";1;"";;;
23;"E3,E4";"SMA-EDGE-SMD";2;"SMA";;;
24;"U$59";"LTE1";1;"";;;
25;"R6,R4,R1";"0603";3;"2.2k";;;
26;"U$40,U$11";"#AUX#0";2;"";;;
27;"U$94";"VIN1";1;"";;;
28;"C1";"1210";1;"22uF";;;
29;"U$58";"GPS0";1;"";;;
30;"J4";"JST-2-SMD";1;"";;;
31;"U$41,U$1";"#1#1";2;"";;;
32;"LOGO5,LOGO2";"QWIIC_5.5MM";2;"QWIIC_LOGO_CONNECTOR";;;
33;"J6";"1X06_NO_SILK";1;"External SIM";;;
34;"U$56,U$57";"SPARKX-MEDIUM";2;"SPARKX-LOGO4";;;
35;"J2,J7";"1X02_NO_SILK";2;"";;;
36;"U$44,U$6";"#4#4";2;"";;;
37;"U$48,U$52";"#RX#0";2;"";;;
38;"U$49,U$54";"#TX#1";2;"";;;
39;"J8,J3";"JST04_1MM_RA";2;"QWIIC_RIGHT_ANGLE";;;
40;"C6";"0603";1;"0.1uF";;;
41;"U$46,U$14";"#RX#6";2;"";;;
42;"U$12";"LTE_1";1;"";;;
43;"U$42,U$4";"#2#2";2;"";;;
44;"J10,J12";"U.FL";2;"U.FL";;;
45;"U$43,U$5";"#3#3";2;"";;;
46;"H5";"STAND-OFF-REFLOW-M2.5";1;"STAND-OFF";;;
47;"U2";"SOT23-5";1;"MCP73831";;;
48;"U4";"M.2-CONNECTOR-E";1;"BLUES NOTECARD";;;
49;"C4,C3";"0603";2;"4.7uF";;;
50;"U$47,U$16";"#TX#5";2;"";;;
51;"C5,C17,C18";"0603";3;"1.0uF";;;
52;"U$45,U$19";"#EN#0";2;"";;;
53;"D5";"LED-0603";1;"RED";;;
54;"FRAME1";"CREATIVE_COMMONS";1;"FRAME-LEDGER";;;
55;"U$29,U$32";"CELLULAR1";2;"";;;
56;"D2";"LED-0603";1;"Yellow";;;
57;"C7";"0603";1;"0.22uF";;;
58;"U$15";"LIPO0";1;"";;;
59;"MEAS0";"COMBO-JUMPER_2_NC_TRACE";1;"";;;
60;"JP1";"SMT-JUMPER_3_2-NC_TRACE_SILK";1;"";;;
61;"U$25";"#SIM_CD#0";1;"";;;
62;"LOGO3";"OSHW-LOGO-MINI";1;"OSHW-LOGOMINI";;;
63;"SIM0";"SMT-JUMPER_2_NO_SILK";1;"";;;
64;"U$36";"#CLK#3";1;"";;;
65;"U$37";"#IO#2";1;"";;;
66;"JP2";"SMT-JUMPER_2_NO_SILK";1;"GPS_ANT_PWR";;;
67;"U$2";"#3V3#2";1;"";;;
68;"U$30";"#RST#0";1;"";;;
69;"U$23";"#VIN#0";1;"";;;
70;"J15";"SIMHOLDER";1;"SIM Socket";;;
71;"U$28";"#MEAS#3";1;"";;;
72;"U$17";"#SCL#1";1;"";;;
73;"U$8";"#SERIAL#1";1;"";;;
74;"U$21";"#SDA#0";1;"";;;
75;"U$35";"#1V8#4";1;"";;;
76;"U$33";"#VIN#1";1;"";;;
77;"U$38";"#RST#5";1;"";;;
78;"U$27";"SIM_HOLDER0";1;"";;;
79;"VIN_LED0";"SMT-JUMPER_2_NC_TRACE_SILK";1;"";;;
80;"U$10";"#I�C#0";1;"";;;
81;"U$13";"#GND#3";1;"";;;
82;"U$24";"#VACT_GPS#0";1;"";;;
83;"U$34";"##CD##1";1;"";;;

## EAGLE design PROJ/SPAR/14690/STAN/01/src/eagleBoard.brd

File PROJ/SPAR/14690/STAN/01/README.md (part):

Contents
========

* [PRPR14690 > Qwiic Proximity VCNL4040](#prpr14690--qwiic-proximity-vcnl4040)
	* [OOMP Parts](#oomp-parts)
	* [Images](#images)
	* [Tags](#tags)
  
![][im]
# PRPR14690 > Qwiic Proximity VCNL4040

- ID: PROJ-SPAR-14690-STAN-01
- Hex ID: PRPR14690
- Name: Qwiic Proximity VCNL4040
- Path: oomlout_OOMP_projects_V2/PROJ/SPAR/14690/STAN/01/
- Description: Qwiic Proximity VCNL4040
- Long Link: [http://oom.lt/PROJ-SPAR-14690-STAN-01](http://oom.lt/PROJ-SPAR-14690-STAN-01)
- Short Link: [http://oom.lt/PRPR14690](http://oom.lt/PRPR14690)

## OOMP Parts

|Image|OOMP ID|Designators|
| :--- | :--- | :--- |
||[CAPC-0603-X-NF100-V50](https://github.com/oomlout/oomlout_OOMP_parts_V2/tree/main/CAPC/0603/X/NF100/V50/)|[C4](https://github.com/oomlout/oomlout_OOMP_parts_V2/tree/main/CAPC/0603/X/NF100/V50/)|
||CAPC-0603-X-UF22D-V10|C1|
||[HEAD-I01-X-PI01-01](https://github.com/oomlout/oomlout_OOMP_parts_V2/tree/main/HEAD/I01/X/PI01/01/)|[J5](https://github.com/oomlout/oomlout_OOMP_parts_V2/tree/main/HEAD/I01/X/PI01/01/)|
||[HEAD-I01-X-PI04-01](https://github.com/oomlout/oomlout_OOMP_parts_V2/tree/main/HEAD/I01/X/PI04/01/)|[J3](https://github.com/oomlout/oomlout_OOMP_parts_V2/tree/main/HEAD/I01/X/PI04/01/)|
||[HEAD-JSTSH-X-PI04-RS](https://github.com/oomlout/oomlout_OOMP_parts_V2/tree/main/HEAD/JSTSH/X/PI04/RS/)|[J2,J4](https://github.com/oomlout/oomlout_OOMP_parts_V2/tree/main/HEAD/JSTSH/X/PI04/RS/)|
||[LEDS-0603-R-STAN-01](https://github.com/oomlout/oomlout_OOMP_parts_V2/tree/main/LEDS/0603/R/STAN/01/)|[D1](https://github.com/oomlout/oomlout_OOMP_parts_V2/tree/main/LEDS/0603/R/STAN/01/)|
||[RESE-0603-X-O102-01](https://github.com/oomlout/oomlout_OOMP_parts_V2/tree/main/RESE/0603/X/O102/01/)|[R3](https://github.com/oomlout/oomlout_OOMP_parts_V2/tree/main/RESE/0603/X/O102/01/)|
||[RESE-0603-X-O103-01](https://github.com/oomlout/oomlout_OOMP_parts_V2/tree/main/RESE/0603/X/O103/01/)|[R1](https://github.com/oomlout/oomlout_OOMP_parts_V2/tree/main/RESE/0603/X/O103/01/)|
||[RESE-0603-X-O222-01](https://github.com/oomlout/oomlout_OOMP_parts_V2/tree/main/RESE/0603/X/O222/01/)|[R4,R5](https://github.com/oomlout/oomlout_OOMP_parts_V2/tree/main/RESE/0603/X/O222/01/)|
||UNMATCHED-UNMATCHED-X-UNMATCHED-01|U2|
||||

## Images

|kicadPcb3dFront<br>|kicadPcb3dBack<br>|kicadPcb3d<br>|pcbdraw<br>|
| :---: | :---: | :---: | :---: |
|pcbdrawBack<br>||||

## Tags

|Tag Name|Tag Code|Tag Value|
| :--- | :--- | :--- |
|OOMP Type|oompType|PROJ|
|OOMP Size|oompSize|SPAR|
|OOMP Color|oompColor|14690|
|OOMP Description|oompDesc|STAN|
|OOMP Index|oompIndex|01|
|Full OOMP ID|oompID|PROJ-SPAR-14690-STAN-01|
|Hex ID (short code)|hexID|PRPR14690|
|name|name|Qwiic Proximity VCNL4040|
|gitRepo|gitRepo|https://github.com/sparkfun/Qwiic_Proximity_VCNL4040|
|gitName|gitName|Qwiic_Proximity_VCNL4040|
|eagleBoard|eagleBoard|/Hardware/Qwiic Proximity Sensor - VCNL4040.brd|
|eagleSchem|eagleSchem|/Hardware/Qwiic Proximity Sensor - VCNL4040.sch|
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
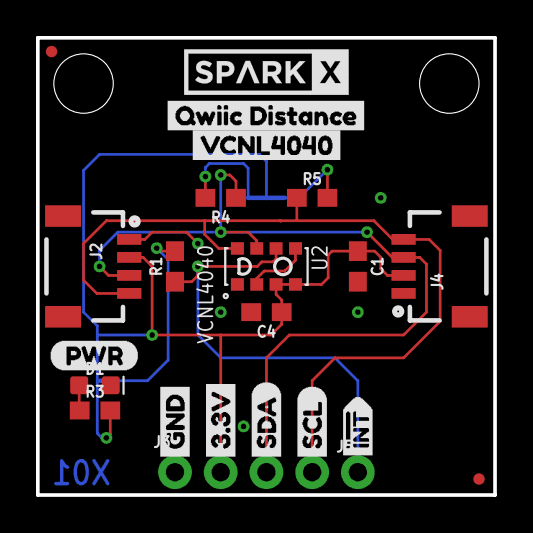
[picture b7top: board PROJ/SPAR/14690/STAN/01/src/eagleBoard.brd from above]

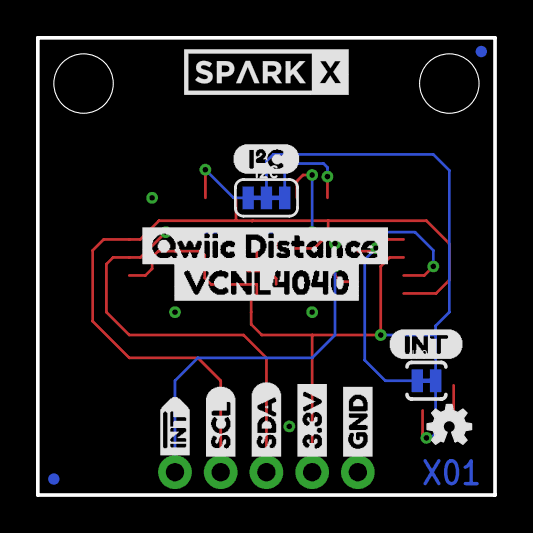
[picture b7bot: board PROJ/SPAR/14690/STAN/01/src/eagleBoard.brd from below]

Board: 2 copper layers, 25.4 x 25.4 mm, 41 parts (15 on the bottom side), 10 nets.

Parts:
C1: 2.2uF; 0603
C4: 0.1uF; 0603
D1: RED; LED-0603
FRAME1: FRAME-LETTER; CREATIVE_COMMONS
I2C: SMT-JUMPER_3_2-NC_TRACE_SILK
J2, J4: SMD; 1X04_1MM_RA
J3: PTH; 1X04_NO_SILK
J5: 1X01_NO_SILK
JP1, JP2, JP5, JP6: FIDUCIALUFIDUCIAL; MICRO-FIDUCIAL
JP3, JP4: STAND-OFF
JP9: INT; PAD-JUMPER-2-NC_BY_TRACE_YES_SILK
LOGO1: OSHW-LOGOMINI; OSHW-LOGO-MINI
R1: 10k; 0603
R3: 1k; 0603
R4, R5: 2.2k; 0603
U2: VCNL4040
U$1, U$2: SPARKX-LOGO4; SPARKX-MEDIUM
U$3, U$22: GND1
U$4, U$21: 3#3V2
U$5, U$27: SDA8
U$6, U$26: SCL9
U$7, U$25: #INT14
U$10: (PWR)
U$11: (I_SUPER2_C)
U$12: (INT)
U$13: VCNL40400
U$14: VCNL40401
U$15: QWIIC_DISTANCE7
U$19: QWIIC_DISTANCE9

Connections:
3.3V: C1.1, C4.1, I2C.2, J2.2, J3.2, J4.2, JP9.2, R3.2, U2.3, U2.4
!INT: J5.1, R1.1, U2.6
GND: C1.2, C4.2, D1.C, J2.1, J3.1, J4.1, U2.1
unnamed: I2C.1, R5.2
unnamed: I2C.3, R4.2
unnamed: D1.A, R3.1
unnamed: JP9.1, R1.2
unnamed: U2.2, U2.5
SCL: J2.4, J3.4, J4.4, R5.1, U2.8
SDA: J2.3, J3.3, J4.3, R4.1, U2.7

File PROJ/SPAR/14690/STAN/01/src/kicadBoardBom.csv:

"Id";"Designator";"Package";"Quantity";"Designation";"Supplier and ref";
1;"U$26,U$6";"SCL9";2;"";;;
2;"U$19";"QWIIC_DISTANCE9";1;"";;;
3;"U$22,U$3";"GND1";2;"";;;
4;"J2,J4";"1X04_1MM_RA";2;"SMD";;;
5;"R4,R5";"0603";2;"2.2k";;;
6;"JP3,JP4";"STAND-OFF";2;"STAND-OFF";;;
7;"U2";"VCNL4040";1;"VCNL4040";;;
8;"U$21,U$4";"3#3V2";2;"";;;
9;"JP2,JP6,JP1,JP5";"MICRO-FIDUCIAL";4;"FIDUCIALUFIDUCIAL";;;
10;"FRAME1";"CREATIVE_COMMONS";1;"FRAME-LETTER";;;
11;"C4";"0603";1;"0.1uF";;;
12;"D1";"LED-0603";1;"RED";;;
13;"R1";"0603";1;"10k";;;
14;"R3";"0603";1;"1k";;;
15;"U$25,U$7";"#INT14";2;"";;;
16;"U$1,U$2";"SPARKX-MEDIUM";2;"SPARKX-LOGO4";;;
17;"J3";"1X04_NO_SILK";1;"PTH";;;
18;"U$13";"VCNL40400";1;"";;;
19;"U$27,U$5";"SDA8";2;"";;;
20;"U$10";"(PWR)";1;"";;;
21;"J5";"1X01_NO_SILK";1;"";;;
22;"C1";"0603";1;"2.2uF";;;
23;"U$12";"(INT)";1;"";;;
24;"U$14";"VCNL40401";1;"";;;
25;"U$11";"(I_SUPER2_C)";1;"";;;
26;"I2C0";"SMT-JUMPER_3_2-NC_TRACE_SILK";1;"";;;
27;"U$15";"QWIIC_DISTANCE7";1;"";;;
28;"LOGO1";"OSHW-LOGO-MINI";1;"OSHW-LOGOMINI";;;
29;"JP9";"PAD-JUMPER-2-NC_BY_TRACE_YES_SILK";1;"INT";;;

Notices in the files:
parts and their libraries:
SparkFun-Resistors: Licensing: Creative Commons ShareAlike 4.0 International - https://creativecommons.org/licenses/by-sa/4.0
SparkFun-Aesthetics: Released under the Creative Commons Attribution Share-Alike 4.0 License
SparkFun-Aesthetics: https://creativecommons.org/licenses/by-sa/4.0
